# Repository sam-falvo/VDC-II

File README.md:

# VDC-II
The VDC-II core is an open source Video Display Controller following in the footsteps, but not a pure clone, of the Commodore 8568 VDC chip.

Link to project on [Hackaday.io](https://hackaday.io/project/170581-vdc-ii).

## Why?
I'm working on a homebrew computer of my own design, called the Kestrel-3.
The Kestrel-3 project, however, is very slow-going, as I'm basically building everything from the ground up.
I was asked if I could instead implement the salient bits of the Kestrel-3's video core, the Configurable Graphics Interface Adapter, or CGIA, for the RC2014 backplane.
That would both speed up development of the Kestrel-3 project, as I'm more focused on individual components, but also can benefit the RC2014 community as well.
I said, "that sounds like a great idea!"

Problem is, I've never built an RC2014 or an expansion board for it before.
And, there are many unknowns along the way:
for example, I've never worked with level shifting logic before,
and interfacing a 25MHz dot-clock circuit to the 7MHz bus of the RC2014 will involve multiple clock domains and its respective complexities.
To get my feet wet, I decided to target a design for the 39-pin RC2014 expansion bus using a small FPGA part, specifically the TinyFPGA BX.

The problem with the TinyFPGA BX is that I'm severely I/O limited!
But, with careful interface design, and a constriction on the number of I/O ports accessible to the host CPU, I was able to fit everything into the pins available.
Also, the TinyFPGA BX provides 16KB of block RAM resources, and that sparked a memory: didn't the C128's VDC chip only have 16KB available to it?

Turns out, yes.  And, it also has a constrained host CPU interface as well.
And looking through the C128's Programmers Reference Manual on how to code for the VDC chip,
I saw that much of the CGIA's feature set was already present in the VDC.  Not everything, but most things for sure!
So, I got to thinking, instead of using the CGIA as the basis,
maybe I can create a version of the VDC chip which can drive a VGA monitor, flexibly.
After all,
the [RomWBW HBIOS](https://github.com/wwarthen/RomWBW/blob/master/Source/HBIOS/cvdu.asm)
software already has a VDC driver available for it, so porting software should be much easier.
(Though, strangely, it goes by the name CVDU or Color VDU in the source tree.)
That's the operating theory, at least.

The VDC-II project was born.

## Description
The VDC-II core aims to be a worthy successor to the original Commodore VDC design.
Unlike the original VDC chip, which runs at NTSC frequencies, the VDC-II core is intended to drive a VGA monitor.

While 100% backward compatibility is not my primary goal, I would continue to strive for it where I can afford to.
There will be some features which will simply work differently between the VDC and VDC-II,
such as how horizontal smooth scrolling works.
Some of these incompatibilities will stem naturally from the fact that we're driving a VGA display instead of a CGA display.
**Disclaimer: I do not have a real Commodore 128 to test behavior with.**
I'm limited to comparing behavior against what the Vice `x128` emulator supports.

## Goals
Most importantly, I want to make a VDC-II core that achieves *basic* feature parity with the original VDC.
This should include supporting all 37 of the original register set.
**Note:** Not all bits of all registers will be supported, or will work *exactly* the same way.
For example, the complex interaction between inter-character gaps and horizontal smooth scrolling might compel me to just leave inter-character gaps out of the design.
(Kind of how `x128` does now.)

Going into future day-dreaming mode,
I'd next implement color palette registers,
giving the VDC-II core more color options.
I'd also support an alternative attribute format which allows for both 16 foreground *and* background colors.

The VDC-II core could conceivably be expanded to support sprites as well, perhaps using an interface not unlike the TMS9918A VDP.
This will be very nice for, e.g., supporting mouse pointers and text cursors while in bitmapped mode (e.g., GEOS/128).

## Resources
These are some handy references and resources I've found to help guide my development.
These might be of interest to you as well.

- https://www.retrobrewcomputers.org/lib/exe/fetch.php?media=boards:ecb:cvdu:8563notes.txt
- [Commodore 128 Programmer's Reference Guide](https://www.pagetable.com/?p=620)

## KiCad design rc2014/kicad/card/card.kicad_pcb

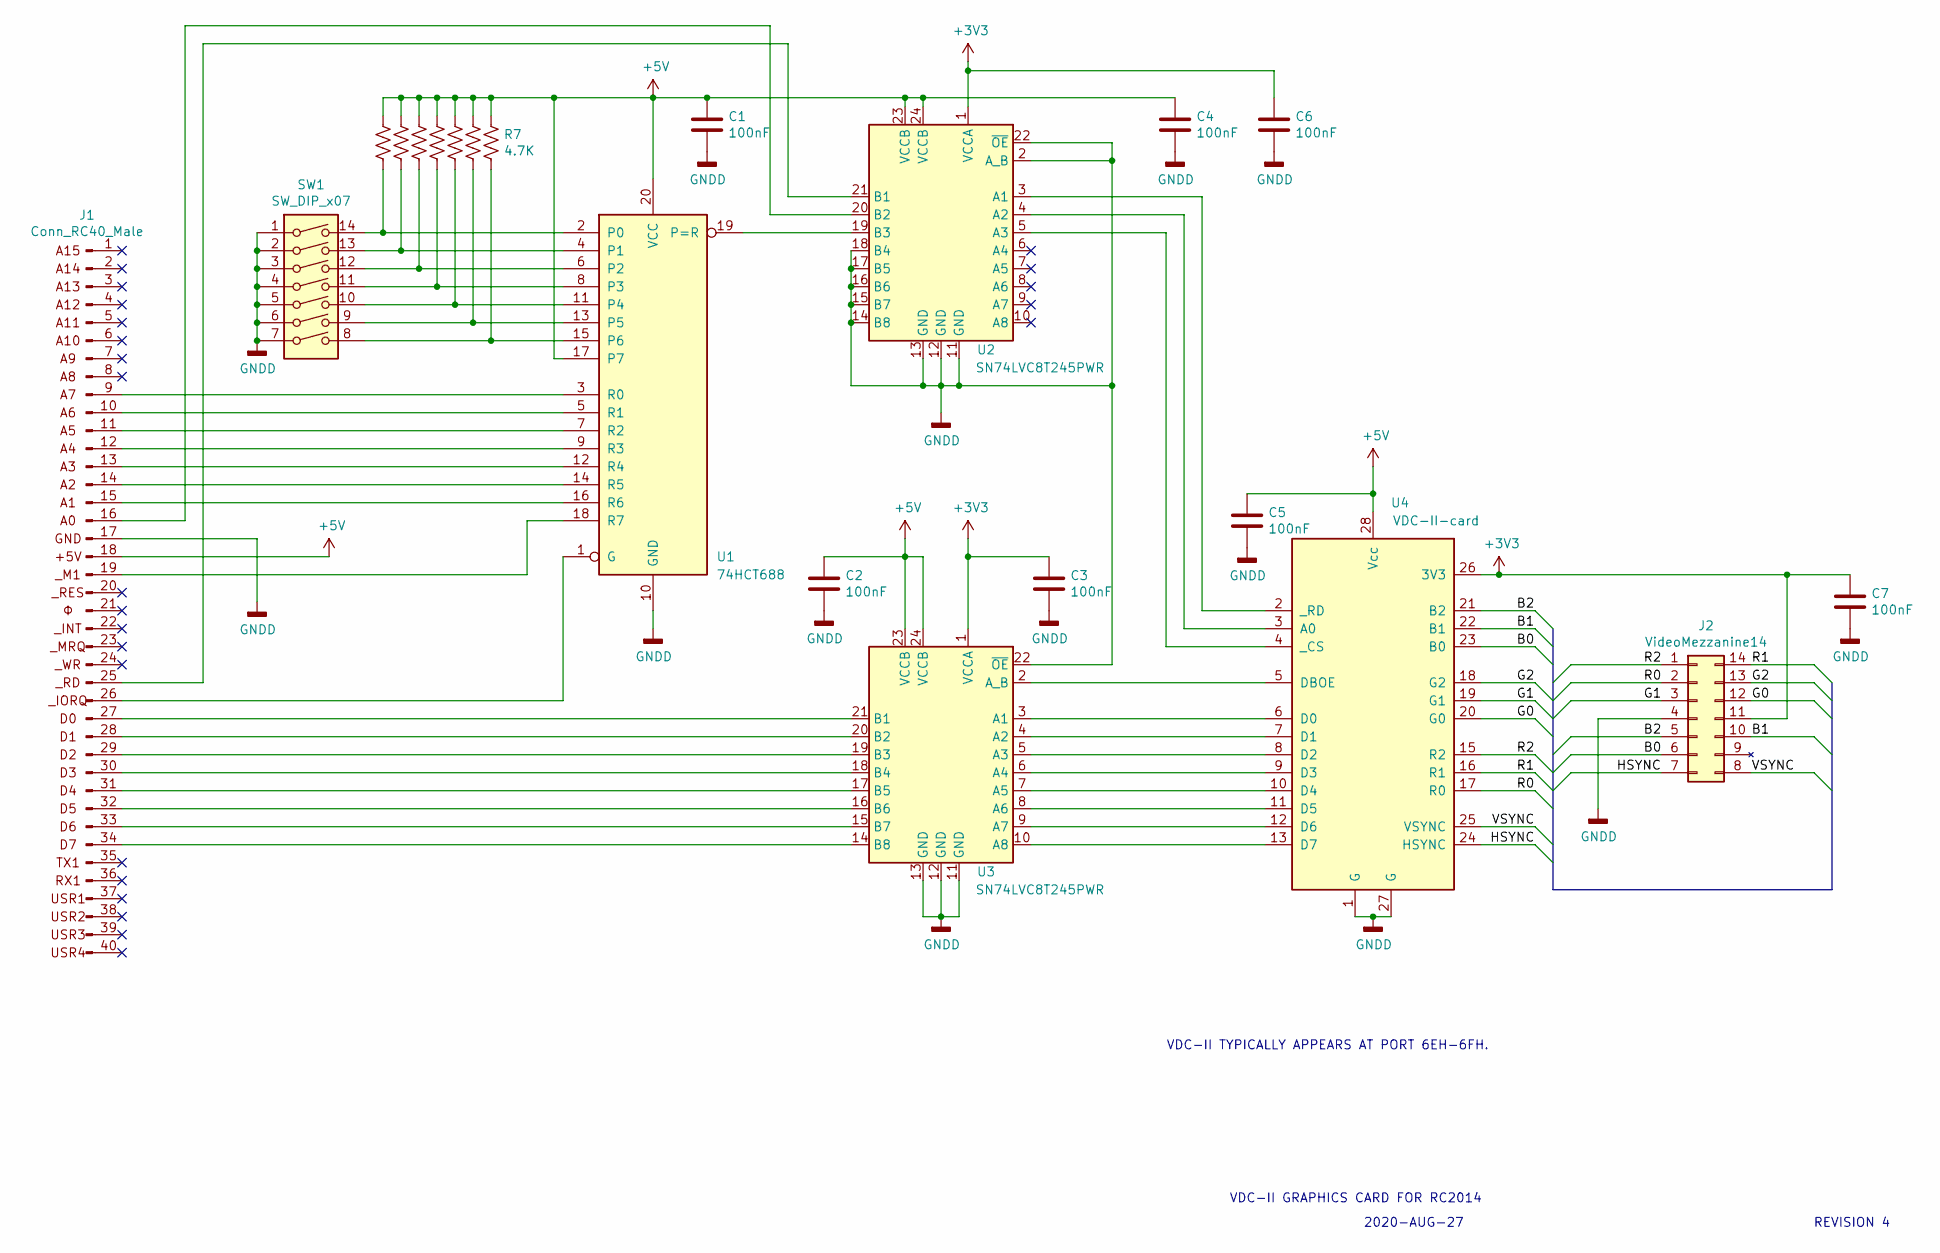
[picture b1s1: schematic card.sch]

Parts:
C1, C2, C3, C4, C5, C6, C7: 100nF; C_Disc_D6.0mm_W4.4mm_P5.00mm
J1: Conn_RC40_Male; PinHeader_1x40_P2.54mm_Vertical
J2: VideoMezzanine14; DIP-14_W7.62mm_Socket
R1, R2, R3, R4, R5, R6, R7: 4.7K; R_Axial_DIN0207_L6.3mm_D2.5mm_P10.16mm_Horizontal
SW1: SW_DIP_x07; DIP-14_W10.16mm
U1: 74HCT688; DIP-20_W7.62mm_Socket
U2, U3: SN74LVC8T245PWR; TSSOP-24_4.4x7.8mm_P0.65mm
U4: VDC-II-card; DIP-28_W15.24mm_Socket

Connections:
+3V3: C3.1, C6.1, C7.1, J2.11 (3V3), U2.1 (VCCA), U3.1 (VCCA), U4.26 (3V3)
+5V: C1.1, C2.1, C4.1, C5.1, J1.18 (+5V), R1.1, R2.1, R3.1, R4.1, R5.1, R6.1, R7.1, U1.17 (P7), U1.20 (VCC), U2.23 (VCCB), U2.24 (VCCB), U3.23 (VCCB), U3.24 (VCCB), U4.28 (Vcc)
/B0: J2.6 (B0), U4.23 (B0)
/B1: J2.10 (B1), U4.22 (B1)
/B2: J2.5 (B2), U4.21 (B2)
/G0: J2.12 (G0), U4.20 (G0)
/G1: J2.3 (G1), U4.19 (G1)
/G2: J2.13 (G2), U4.18 (G2)
/HSYNC: J2.7 (HSYNC), U4.24 (HSYNC)
/R0: J2.2 (R0), U4.17 (R0)
/R1: J2.14 (R1), U4.16 (R1)
/R2: J2.1 (R2), U4.15 (R2)
/VSYNC: J2.8 (VSYNC), U4.25 (VSYNC)
GNDD: C1.2, C2.2, C3.2, C4.2, C5.2, C6.2, C7.2, J1.17 (GND), J2.4 (GND), SW1.1, SW1.2, SW1.3, SW1.4, SW1.5, SW1.6, SW1.7, U1.10 (GND), U2.2 (A_B), U2.11 (GND), U2.12 (GND), U2.13 (GND), U2.14 (B8), U2.15 (B7), U2.16 (B6), U2.17 (B5), U2.18 (B4), U2.22 (~OE), U3.11 (GND), U3.12 (GND), U3.13 (GND), U3.22 (~OE), U4.1 (G), U4.27 (G)
unnamed: J1.9 (A7), U1.3 (R0)
unnamed: J1.10 (A6), U1.5 (R1)
unnamed: J1.11 (A5), U1.7 (R2)
unnamed: J1.12 (A4), U1.9 (R3)
unnamed: J1.13 (A3), U1.12 (R4)
unnamed: J1.14 (A2), U1.14 (R5)
unnamed: J1.15 (A1), U1.16 (R6)
unnamed: J1.16 (A0), U2.20 (B2)
unnamed: J1.19, U1.18 (R7)
unnamed: J1.25, U2.21 (B1)
unnamed: J1.26, U1.1 (G)
unnamed: J1.27, U3.21 (B1)
unnamed: J1.28, U3.20 (B2)
unnamed: J1.29, U3.19 (B3)
unnamed: J1.30, U3.18 (B4)
unnamed: J1.31, U3.17 (B5)
unnamed: J1.32, U3.16 (B6)
unnamed: J1.33, U3.15 (B7)
unnamed: J1.34, U3.14 (B8)
unnamed: R1.2, SW1.14, U1.2 (P0)
unnamed: R2.2, SW1.13, U1.4 (P1)
unnamed: R3.2, SW1.12, U1.6 (P2)
unnamed: R4.2, SW1.11, U1.8 (P3)
unnamed: R5.2, SW1.10, U1.11 (P4)
unnamed: R6.2, SW1.9, U1.13 (P5)
unnamed: R7.2, SW1.8, U1.15 (P6)
unnamed: U1.19 (P=R), U2.19 (B3)
unnamed: U2.3 (A1), U4.2 (_RD)
unnamed: U2.4 (A2), U4.3 (A0)
unnamed: U2.5 (A3), U4.4 (_CS)
unnamed: U3.2 (A_B), U4.5 (DBOE)
unnamed: U3.3 (A1), U4.6 (D0)
unnamed: U3.4 (A2), U4.7 (D1)
unnamed: U3.5 (A3), U4.8 (D2)
unnamed: U3.6 (A4), U4.9 (D3)
unnamed: U3.7 (A5), U4.10 (D4)
unnamed: U3.8 (A6), U4.11 (D5)
unnamed: U3.9 (A7), U4.12 (D6)
unnamed: U3.10 (A8), U4.13 (D7)

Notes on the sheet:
VDC-II GRAPHICS CARD FOR RC2014
REVISION 4
2020-AUG-27
VDC-II TYPICALLY APPEARS AT PORT 6EH-6FH.

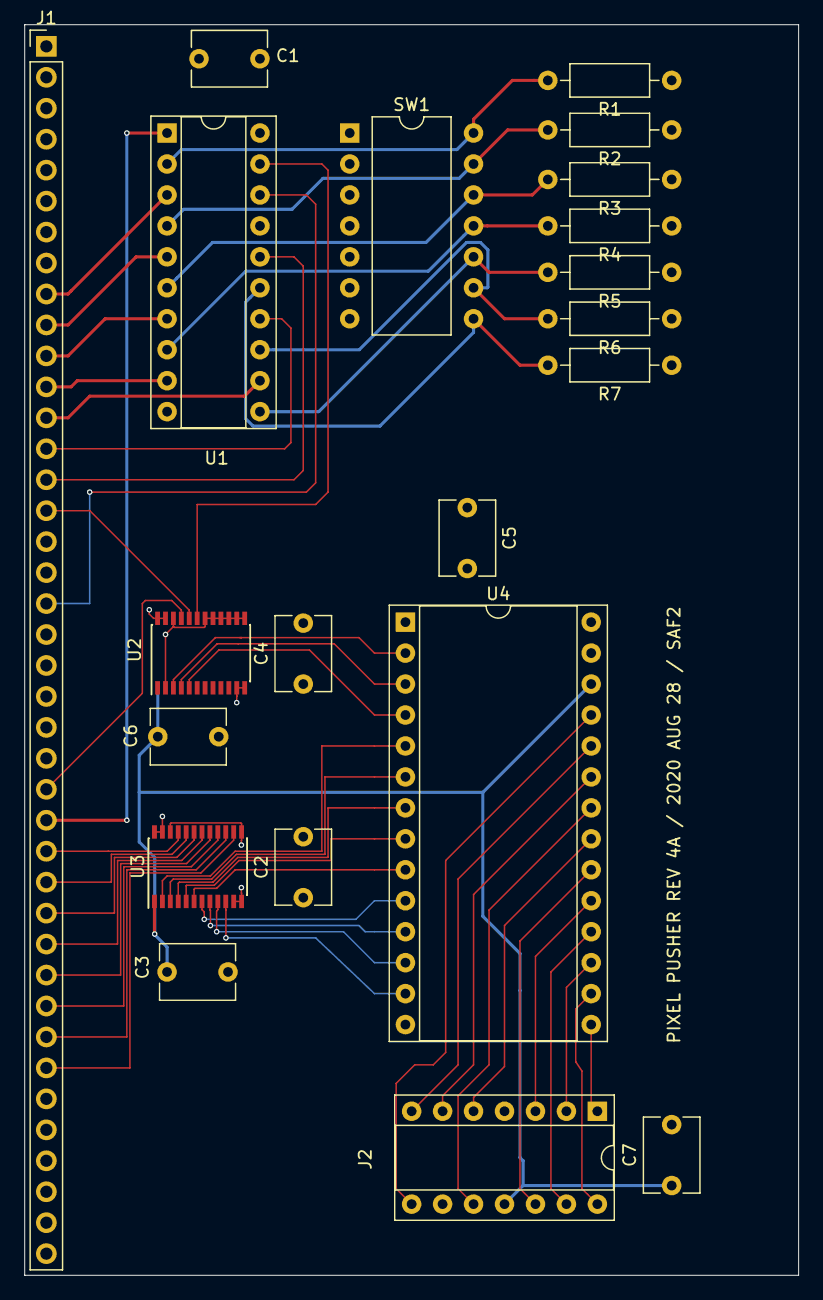
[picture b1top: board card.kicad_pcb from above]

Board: 4 copper layers, 63.5 x 102.6 mm, 21 parts (0 on the bottom side), 53 nets.

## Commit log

2020-03-21 Refine rationale
2020-03-21 Initial test harness for hsync generation
2020-03-21 Hsync module (#2)
    * Fixes #1. HSYNC generation circuit.
    * Refactor
    * Add test for prover
    * refactor again
    * Refactor again.
    * Remove dead code
2020-03-22 Base HSYNC generator on characters instead of pixels. Fixes #3. (#4)
2020-03-24 Hsync regs (#6); fixes #5.
    * initial scaffold for a generic register
    * Implements split- and read/write-registers.
    These can be used to build up a register set.
    * Add things for make clean to remove
    * Scaffold for VDC-II register set module
    * 8-bit register set interface; easier than using Reg
2020-03-25 Z80 bus interface. Fixes #7. (#8)
    * Initial skeleton for Host Bus module.
    * Output enable driver control for data bus
    * This completes the Z80 host processor bus interface.
    * Refactor
2020-03-27 Sync polarity (#10)
    * Fixes #9. Supports sync polarity settings.
    * Default polarity bits to 1
2020-03-27 Update docstring
2020-03-27 Fixes #11. Decrement sync counter width only on last column of character. (#12)
2020-03-27 First attempt at a top module.
    This simple file can be invoked with:
    python top.py
    This should build (but not program) the TinyFPGA BX bitstream. The code
    will need to be changed (do_program=True instead of =False) to support
    programming as well.
2020-03-30 Pll (#13)
    * PLL and reworked I/O to match physical wiring.
    * New pin assignment.
    * Forgot to add pll.py
2020-03-30 Introduce simulation of hostbus <-> register set.
    Manual testing of the FPGA indicates that the host bus interface does
    not work. It behaves as if address line is always low, regardless of
    the state of CS# and RD#.
2020-03-30 Use default clock domain for PLL input
2020-03-30 KiCAD schematics for current test hardware
2020-03-30 Update README to include Hackaday link.
2020-04-12 Revision 2 w/ new level shifters
2020-04-15 Support for 74LVC8T245PWR level shifters
2020-04-19 Factor sync generation into a reusable module. (#14)
    * Factor sync generation into a reusable module.
    This step will, I hope, make it easier to instantiate a HSYNC and
    a VSYNC generator with minimum code duplication.
    * Remove references to HSync module.
    * Complete refactoring of sync generator logic
    * Remove dead code
2020-04-19 Switch from count-up to count-down character counter.
    The VDC appears to use down-counters for triggering events, such as
    flagging when to start shifting dots to teh screen, even though some
    registers (e.g., light-pen) appear to make use of up-counters. I don't
    anticipate using light-pens with the VDC-II (though the registers will
    remain reserved for future restoration of the facility if someone wants
    it). Therefore, switching to using down-counters optimizes for the more
2020-04-24 Yet another sync generator.
    This one more closely models the origial 6545 CRTC behavior, which is
    what the 8563 inherits. If I can add support for horizontal total
    adjustment, then I can reuse the same module for vertical sync as well.
2020-04-25 Horizontal Total Adjust support.
2020-04-25 dot clock enable input.
    Added a master enable signal to control which dot clocks are relevant,
    even when hclken output isn't asserted. This is required because the
    total adjust functionality always works on units of pixels/lines, not on
    units of characters.
2020-04-25 Refactor HSYNC generator into something generic.
2020-04-25 Remove old sync generator logic
2020-04-25 refactor
2020-04-25 This should complete the VSYNC interface.
    In addition to generating both HSYNC and VSYNC, this circuit should also
    drive the display with a test pattern which illustrates where character
    cells reside on the playfield.
2020-04-25 Bug fix: only low bit of register address was significant.
2020-04-25 bug: vertical sync happened 7 to 8x too fast.
    Caused by hsyncgen.rastclken signal occupying an entire character cell.
    Fix is to AND it with hsyncgen.xclken.
    NOTE: There is still an additional bug in this version: the total adjust
    setting **adds** to the width of the vertical sync, instead of (or
    perhaps in addition to?) delaying reset of vertical counter to 0.
2020-04-25 Fix vsync pulse width bug
2020-04-25 Restore grid patteron on test display
2020-04-25 Vsync (#17). Fixes #15
    * Switch from count-up to count-down character counter.
    The VDC appears to use down-counters for triggering events, such as
    flagging when to start shifting dots to teh screen, even though some
    registers (e.g., light-pen) appear to make use of up-counters. I don't
    anticipate using light-pens with the VDC-II (though the registers will
    remain reserved for future restoration of the facility if someone wants
2020-04-25 Add properly blanked test video output
2020-05-05 Datasheet for SyncGen module
2020-05-05 Remove tabs
2020-05-08 MPE (#19)
    * First code for MPE
    * Record prefetched data in holding register
    * Let a host CPU read data from video memory.
    * Implement update location registers
    * Generate read command pulse from host interface
    * Strobe to detect data port reads
2020-05-09 Fixes #21 by denying display enable until end of total adjust. (#22)
2020-05-16 Record an easy to use blank module template
2020-05-16 remove phantom I/Os
2020-05-17 WIP: address generator logic for video fetch.
    I don't do anything with the fetched data yet; but this *seems* like it
    should work to fetch color or monochrome text or bitmapped mode data.
2020-05-18 Data receiver logic
2020-05-22 execute permission on tester.sh
2020-05-22 Initial work on dot shifter.
    This implements the core logic for horizontal smooth scroll. This logic
    will be instrumental in building out the remainder of the dot shifter.
2020-05-24 Implemented ROM-based "strip buffer".
    The ROM-based strip buffer is designed to test our ability to put pixels
    on the display from "video memory" without implementing the complexity
    of a memory arbiter and video fetch engine just yet.
    It confirms that attributes are properly aligned with pixels, and that
    horizontal smooth scroll continues to work as expected in the face of
    these new changes.
2020-05-25 Block RAM arbiter
2020-05-25 Refactor shifter
2020-05-25 WHY?! WHY DID THIS DEF DISAPPEAR?!
    WHAT THE FUCK HAPPENED? WHY DID THIS DEFINITION DISAPPEAR? I **NEVER**
    REMOVED THIS DEFINITION IN MY EDITOR!
2020-05-25 Pass asize through
2020-05-25 Refactor video fetch engine
2020-05-25 Strip buffer
2020-05-25 Expose atrbase to other subcircuits
2020-05-25 Reset atrptr at start of video frame
2020-05-25 Vertical smooth scroll, attr/char ptrs
2020-05-25 WIP: monochrome bitmap almost working.
    Bitmap generation and vertical scrolling doesn't quite work.
    If I enable attributes, I can see video memory does contain alternating
    sequences of $AA and $55 bytes (see GREY.BAS to change these defaults).
    However, instead of the stipple pattern I expected, I get one bitmap row
    repeated for every raster row in a character row. Except, that is, for
    bitmap row 0.
2020-05-25 Fixes bad fetch pointer values at top raster row.
    Works for bitmap and character modes as far as I can tell so far.
2020-05-26 Record my test programs
2020-05-26 Bitmap mode (#27)
    * Record an easy to use blank module template
    * remove phantom I/Os
    * WIP: address generator logic for video fetch.
    I don't do anything with the fetched data yet; but this *seems* like it
    should work to fetch color or monochrome text or bitmapped mode data.
    * Data receiver logic
2020-05-30 User environment framework for clock demo
2020-05-30 Displays clock and paused indicator
2020-05-30 Ticks clock. But, still too fast.
    Not sure if this is a VDC hardware bug or not. It doesn't *seem* like
    it should be a software bug, though; early evidence points to a VDC bug
    or a misunderstanding of how the VSYNC flag works.
2020-05-30 Solve callback firing too fast issue identified prior.
2020-05-30 Pause feature, for real.
2020-06-16 First cut at VDC-Forth
2020-06-18 Create dir fir cmdline work
2020-06-18 Makefile
2020-06-18 Remove duplicate scripts
2020-06-18 Move VDC tests to final resting place
2020-06-18 First code for cmdline tests
2020-06-18 Add TestNotEqual procedure to unit test engine
2020-06-20 Low-level Terminal Input Buffer routines.
2020-06-23 Get basic typing and backspace working on-screen
2020-06-23 Fix tcmdline broken build
2020-06-24 Remove OK from the screen when interpreting
2020-06-26 Compare strings for equality.
2020-06-26 Forgot to add tstreq.asm to clean target
2020-07-07 Implement equivalent of WORD (InterpNextWord).
    Parses next word from input string, if any exists. Puts counted-string
    version of the parsed word at HERE, ready for comparison with StrCompare
    procedure. Counted string can also be used in the construction of new
    dictionary headers later on.
2020-07-08 Confirm we can parse words sequentially
2020-07-17 Support code to find a definition and execute it.
    Not tied into the CLI yet.
2020-07-17 Tie BYE and PAGE into the dictionary.
    First time a user can type a command and execute something!
2020-07-18 division routines
2020-07-20 Fill buffer with contents of data stack
2020-07-20 Paint stack contents interactively.
    If I do say so, this came out a lot better than I'd anticipated!
2020-08-02 Refine usecase to support arbitrary numeric input.
2020-08-02 Support unsigned numbers on the command line.
2020-08-02 Support negative and positive notation
2020-08-03 Start fleshing out the interpreted dictionary
2020-08-28 R4 schematic for VDC-II card
2020-08-28 Repin U4
2020-08-28 Finish PCB layout for main PP board
2020-08-29 Small revisions to make things work for OSHPark.
2020-09-23 Rev 4B of PCB layout.
    - Fix missing pin 1 indicators.
    - Fix missing 3.3V supply connection on U2.
    - Fix DIP switch footprint size.
    - Rename PCB to BX-PLORER
    - Pixel Pusher will be (BX-PLORER + VGA mezzanine).
    - Separate mezzanine planned for PS/2 keyboard and mouse.
2020-09-24 Reconfigure VDC-II for new J2 mezzanine port
2020-10-29 Improve tester.sh error handling
